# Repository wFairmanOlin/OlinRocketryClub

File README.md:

# OlinRocketryClub
Repo for a self-designed flight computer

## First Project - Phoenix I
1. 3-axis accelerometer
2. data storing functionality to SD card

## Second Project - Peregrine I
This board is intended to record flight data and transmit telemetry while maintaining a slim and lightweight profile.

### Main Components:
1. Barometer, Accelerometer, Gyroscope
2. Data storage to SD card
3. RF Transmitter
4. Battery

## How to Clone this Repo (Ubuntu)
1. Use the Ctrl+Alt+t command to open your terminal. 
2. Use the `cd` command to switch to the directory you want to save this repo in.
3. Copy and paste the code below into your terminal (hint: use Ctrl+Shift+v to paste into the terminal)
```
git clone https://github.com/wFairmanOlin/OlinRocketryClub.git
```

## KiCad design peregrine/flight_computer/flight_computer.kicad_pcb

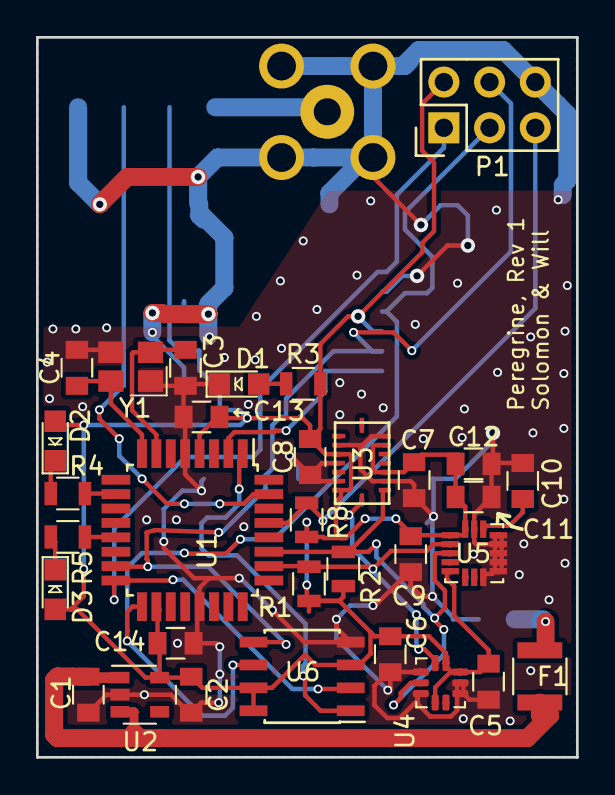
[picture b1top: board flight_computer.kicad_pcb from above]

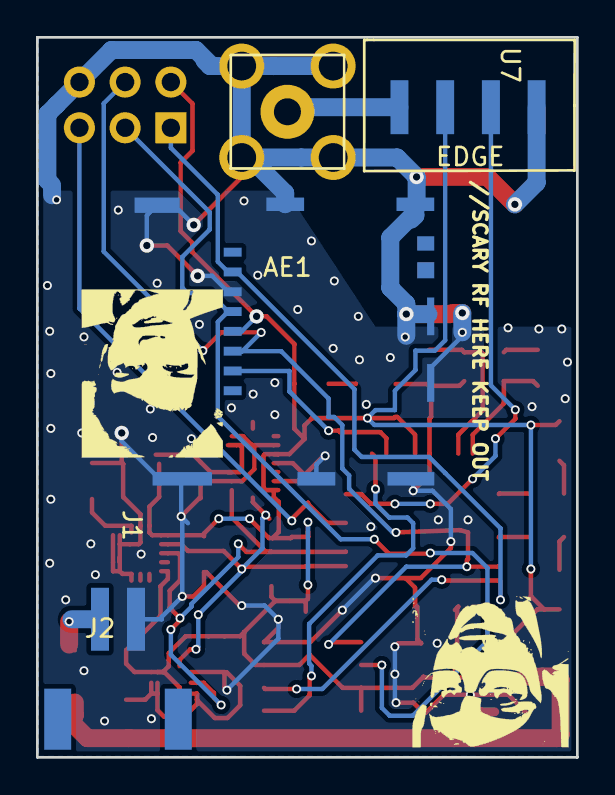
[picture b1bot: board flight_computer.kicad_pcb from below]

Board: 2 copper layers, 30.0 x 40.0 mm, 36 parts (4 on the bottom side), 22 nets.

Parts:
AE1: DS-SMA-EDGE-4; 5-1814400-1
C1, C2: C_1uF; C_0805_OEM
C3, C4: C_30pF; C_0805_OEM
C5, C6, C7, C8, C12, C14: C_0.1uF; C_0805_OEM
C9: 10nF; C_0805_OEM
C10: C_47uF; C_0805_OEM
C11: 2.2uF; C_0805_OEM
D1, D2, D3: LED_0805; LED_0805_OEM
F1: Fuse; Fuse_1210
J1: Micro_SD_Card_Det; SD-Card
J2: Conn_01x02_Male; JST_90DEG_2PIN
P1: CONN_02X03; Pin_Header_Straight_2x03
R1, R2: 4.7kR; R_0805_OEM
R3, R4, R5: R_200; R_0805_OEM
R8: R_10k; R_0805_OEM
U1: ATmega328PB-AU; TQFP-32_7x7mm_P0.8mm
U2: MIC5504-3.3YM5; SOT-23-5
U3: BMI088; BMI088-LGA16
U4: BMP388; ST_HLGA-10_2.5x2.5mm_P0.6mm_LayoutBorder3x2y
U5: ICG-20660; LGA-16_3x3mm_P0.5mm_LayoutBorder3x5y
U6: AT25SF041; SOIC-8_3.9x4.9mm_P1.27mm
U7: RFTRANS434MHZ
Y1: Crystal_SMD; Crystal_SMD_FA238
←C13: C_0.1uF; C_0805_OEM

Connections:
+3V3: C2.1, C5.1, C6.1, C7.2, C8.2, C9.1, C11.1, C12.1, C14.2, D2.2, D3.2, J1.4, P1.2, R1.1, R2.1, R3.2, R8.1, U1.4, U1.18, U2.5, U3.3, U3.7, U3.11, U3.14, U4.1, U4.6, U4.10, U5.1, U5.5, U5.16, U6.3, U6.7, U6.8, U7.3, ←C13.1
+BATT: C1.1, F1.1, U2.1, U2.3
/CS_FLASH: U1.1, U6.1
/CS_SD: J1.2, U1.2
/LED_B: R4.2, U1.10
/LED_R: R5.2, U1.13
/MISO: J1.7, P1.1, U1.16, U6.2
/MOSI: J1.3, P1.4, U1.15, U6.5
/RST: P1.5, R8.2, U1.29
/SCK: J1.5, P1.3, U1.17, U6.6
/SCL: R1.2, U1.26, U3.8, U4.2, U5.2
/SDA: R2.2, U1.27, U3.9, U4.4, U5.3
/TXD: U1.31, U7.2
/XTAL1: C3.1, U1.7, Y1.1
/XTAL2: C4.1, U1.8, Y1.3
GND: AE1.2, C1.2, C2.2, C3.2, C4.2, C5.2, C6.2, C7.1, C8.1, C9.2, C10.2, C11.2, C12.2, C14.1, D1.1, J1.6, J1.11, J2.2, P1.6, U1.5, U1.21, U2.2, U3.2, U3.4, U3.6, U3.10, U3.15, U4.3, U4.5, U4.8, U4.9, U5.8, U5.9, U5.10, U5.11, U5.12, U5.13, U5.15, U6.4, U7.1, Y1.2, Y1.4, ←C13.2
unnamed: AE1.1, U7.4
unnamed: C10.1, U5.14
unnamed: D1.2, R3.1
unnamed: D2.1, R4.1
unnamed: D3.1, R5.1
unnamed: F1.2, J2.1

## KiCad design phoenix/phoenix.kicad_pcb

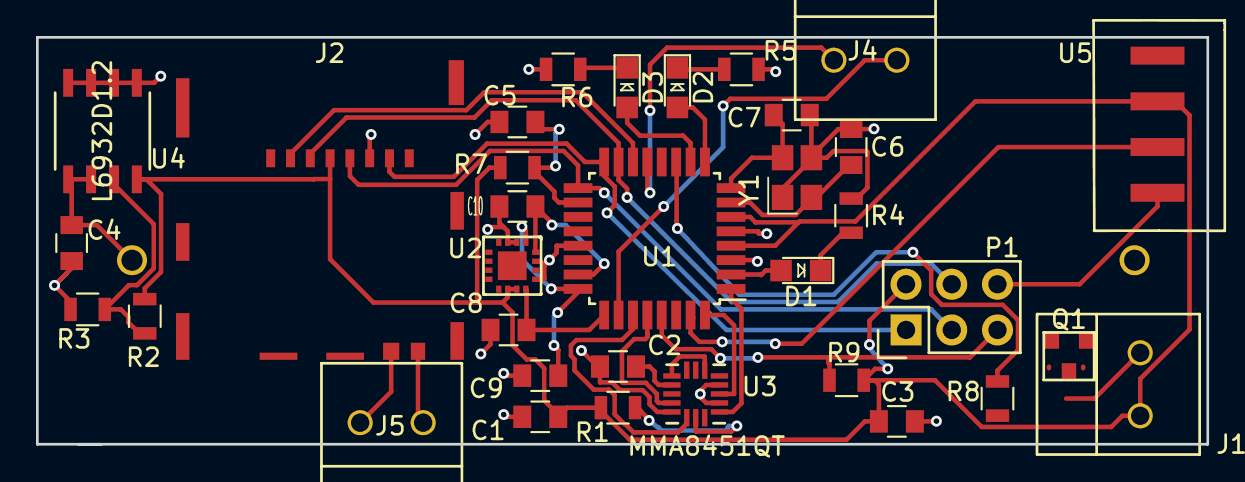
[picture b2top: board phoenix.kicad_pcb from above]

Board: 2 copper layers, 65.0 x 22.6 mm, 35 parts (1 on the bottom side), 35 nets.

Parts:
BT1: 3.7V Lipo; battery_holder
C1, C2: C_0.1uF; C_0805_OEM
C3, C4: C_10uF; C_0805_OEM
C5: C_100pF; C_0805_OEM
C6, C7: C_30pF; C_0805_OEM
C8, C9, C10: C_1000pF; C_0805_OEM
D1, D2, D3: LED_0805; LED_0805_OEM
J1, J4, J5: Ultrafit_2
J2: Micro_SD_Card_Det; SD-Card
P1: CONN_02X03; Pin_Header_Straight_2x03
Q1: IRLML6344; IRLML6344TRPBFCT-ND
R1, R8, R9: R_10k; R_0805_OEM
R2: 9K; R_0805_OEM
R3: 5K; R_0805_OEM
R4, R5, R6: R_200; R_0805_OEM
R7: R_100; R_0805_OEM
U1: ATMEGA328P-AU; TQFP-32_7x7mm_Pitch0.8mm
U2: ADX377; ADXL377
U3: MMA8451QT
U4: L6932D1.2; L6932D1.2TR
U5: RFTRANS434MHZ
Y1: Crystal_SMD; Crystal_SMD_FA238

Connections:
+3V3: C1.1, C3.1, J1.1, J2.4, P1.2, R1.2, R2.1, R7.1, R9.1, U1.4, U1.6, U2.14, U2.15, U4.4, U5.3
/BYP: C2.1, U3.2
/INT1: U1.32, U3.11
/INT2: U1.1, U3.9
/MISO: J2.7, P1.1, U1.16
/MOSI: J2.3, P1.4, U1.15
/PB6: C6.1, U1.7, Y1.1
/PB7: C7.1, U1.8, Y1.3
/PLED1: D1.2, U1.2
/PLED2: D2.2, U1.9
/PLED3: D3.2, U1.10
/RESET: P1.5, R9.2, U1.29
/SCK: J2.5, P1.3, U1.17
/SCL: U1.28, U3.4
/SDA: U1.27, U3.6
/SEPERATE: Q1.1, R8.1, U1.11
/Spi_config: J2.2, U1.14
/TX: U1.31, U5.2
/VIN: BT1.1, C4.1, U4.1, U4.2
/XOUT: C9.1, U1.24, U2.5
/YOUT: C10.1, U1.23, U2.4
/ZOUT: C8.1, U1.25, U2.16
GND: BT1.2, C1.2, C2.2, C3.2, C4.2, C5.2, C6.2, C7.2, C8.2, C9.2, C10.2, J2.6, P1.6, Q1.2, R3.2, R4.2, R5.2, R6.2, R8.2, U1.3, U1.5, U1.21, U2.1, U2.3, U2.6, U2.7, U3.5, U3.10, U3.12, U4.5, U4.6, U4.7, U4.8, U5.1, Y1.2, Y1.4
unnamed: C5.1, R7.2, U1.18
unnamed: D1.1, R4.1
unnamed: D2.1, R5.1
unnamed: D3.1, R6.1
unnamed: J1.2, Q1.3
unnamed: J2.9, J5.2
unnamed: J2.10, J5.1
unnamed: R1.1, U3.7
unnamed: R2.2, R3.1, U4.3
unnamed: J4.1, U1.13
unnamed: J4.2, U1.26
unnamed: U3.1, U3.14

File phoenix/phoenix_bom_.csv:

Component,Description,Part,References,Value,Footprint,Quantity Per PCB,Datasheet,Package,MPN,MFN,PurchasingLink,PurchasingLinks
1,single battery cell,Battery_Cell,BT1,3.7V Lipo,battery_holder,1,,,,,,
2,,C_0.1uF,C1 C2,C_0.1uF,C_0805_OEM,2,http://datasheets.avx.com/X7RDielectric.pdf,Value,478-3352-1-ND,Digi-Key,https://www.digikey.com/products/en?keywords=478-3352-1-ND,
3,,C_100pF,C5,C_100pF,C_0805_OEM,1,https://content.kemet.com/datasheets/KEM_C1003_C0G_SMD.pdf,Value,399-1122-1-ND,Digi-Key,https://www.digikey.com/product-detail/en/kemet/C0805C101J5G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,
4,,C_10uF,C3 C4,C_10uF,C_0805_OEM,2,http://datasheets.avx.com/cx5r.pdf,Value,478-5167-1-ND,Digi-Key,https://www.digikey.com/product-detail/en/avx-corporation/08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,
5,,C_30pF,C6 C7,C_30pF,C_0805_OEM,2,https://media.digikey.com/pdf/Data%20Sheets/Samsung%20PDFs/C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,Value,1276-1130-1-ND,Digi-Key,https://www.digikey.com/product-detail/en/samsung-electro-me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,
6,,LED_0805,D1 D2 D3,LED_0805,LED_0805_OEM,3,http://www.osram-os.com/Graphics/XPic9/00078860_0.pdf,Value,475-1410-1-ND,Digi-Key,https://www.digikey.com/products/en?keywords=475-1410-1-ND,
7,Micro SD Card Socket with card detection pins,Micro_SD_Card_Det,J2,Micro_SD_Card_Det,SD-Card,1,https://www.hirose.com/product/en/download_file/key_name/DM3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,,,,,
8,,Ultrafit_2,J1,Ultrafit_2,Ultrafit_2_RA,1,,Value,WM11570-ND,Digi-Key,https://www.digikey.com/product-detail/en/molex-llc/17228611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,
9,,CONN_02X03,P1,CONN_02X03,Pin_Header_Straight_2x03,1,http://portal.fciconnect.com/Comergent//fci/drawing/67996.pdf,Value,609-3234-ND,Digi-Key,https://www.digikey.com/product-detail/en/amphenol-fci/67997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,
10,"200V Vds, N-Channel MOSFET, 2.6V Logic Level, TO-92",IRLML6344,Q1,IRLML6344,IRLML6344TRPBFCT-ND,1,https://www.infineon.com/dgdl/irlml6344pbf.pdf?fileId=5546d4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,,,,,https://www.digikey.com/product-detail/en/infineon-technolog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
11,,5K,R3,5K,R_0805_OEM,1,,,,,,
12,,5K,R2,9K,R_0805_OEM,1,,,,,,
13,,R_100,R7,R_100,R_0805_OEM,1,https://www.seielect.com/Catalog/SEI-rncp.pdf,Value,RNCP0805FTD100RCT-ND,Digi-Key,https://www.digikey.com/products/en?keywords=RNCP0805FTD100RCT-ND,
14,,R_10k,R1 R8 R9,R_10k,R_0805_OEM,3,http://www.bourns.com/data/global/pdfs/CRS.pdf,Value,CRS0805-FX-1002ELFCT-ND,Digi-Key,https://www.digikey.com/products/en?keywords=CRS0805-FX-1002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,
15,,R_200,R4 R5 R6,R_200,R_0805_OEM,3,https://www.seielect.com/Catalog/SEI-RMCF_RMCP.pdf,Value,RMCF0805JT200RCT-ND,Digi-Key,https://www.digikey.com/products/en?keywords=RMCF0805JT200RCT-ND,
16,"TQFP32, 16k Flash, 1kB SRAM, 512B EEPROM",ATMEGA328P-AU,U1,ATMEGA328P-AU,TQFP-32_7x7mm_Pitch0.8mm,1,http://www.atmel.com/images/atmel-8271-8-bit-avr-microcontro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,,,,,
17,,L6932D1.2,U4,L6932D1.2,L6932D1.2TR,1,,,,,,
18,,MMA8451QT,U3,MMA8451QT,MMA8451QT,1,,,,,,https://www.digikey.com/products/en?mpart=MMA8451QT&v=568
19,,Crystal_SMD,Y1,Crystal_SMD,Crystal_SMD_FA238,1,https://support.epson.biz/td/api/doc_check.php?dl=brief_FA-2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,Value,SER3686CT-ND,Digi-Key,https://www.digikey.com/products/en?keywords=SER3686CT-ND,





Component Groups:,19
Component Count:,28
Fitted Components:,28
Number of PCBs:,1
Total components:,28
Schematic Version:,
Schematic Date:,
BoM Date:,Thu 12 Apr 2018 10:37:11 PM EDT
Schematic Source:,/home/william/Desktop/OlinRocketryClub/phoenix/phoenix.sch
KiCad Version:,Eeschema 4.0.7-e2-6376~58~ubuntu16.04.1

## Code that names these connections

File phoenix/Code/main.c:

#include <avr/io.h>
#include <util/delay.h>
#include <avr/interrupt.h>

#define F_CPU           4000000UL
#define PORT_LED        PORTD
#define REG_LED         DDRD
#define LED1            PD4
#define LED2            PD5
#define LED3            PD6

#define PORT_A          PORTC
#define REG_A           DDRC
#define YOUT            PC0
#define XOUT            PC1
#define ZOUT            PC2

#define FLAG_EMATCH     0

uint8_t gFlag = 0x00;

uint8_t gY = 0x00;
uint8_t gX = 0x00;
uint8_t gZ = 0x00;

unsigned long gCounter = 0x00;

/* TODO FOR WEDNESDAY */
//Get timer working
//Write to sd-card
//Get transistor working
//Calibrate accelerometer data
//Create function for appogee using accel data

ISR(TIMER0_COMPA_vect){
    //TODO fix
    //Currently ticks at 4hz
    gCounter++;
    if (gCounter > 60){
        gFlag |= _BV(FLAG_EMATCH);
    }
    if(gCounter > 80){
        gFlag |= _BV(3);
    }

}

void initTimer(void) {
    //TODO
    //FOR 16M1, configure for 328P
    TCCR0A = _BV(WGM01);    // Set up 8-bit timer in CTC mode
    TCCR0B = 0x05;          // clkio/1024 prescaler
    TIMSK0 |= _BV(OCIE0A);
    OCR0A = 0xFF;
}


void initADC(void) {
    //Get the Analog to Digital Converter started (ADC)
    ADCSRA |= _BV(ADEN) | _BV(ADPS2) | _BV(ADPS0);

    //Enable interal reference voltage
    // ADCSRB |= _BV(AREFEN);

    //Set internal reference voltage as AVcc
    ADMUX |= _BV(REFS0);

    //Reads by default from ADC0 (pin 11)
    //This line is redundant. The timer
    ADMUX |= _BV(0x00);
}

void readAC(void){
    ADMUX = _BV(REFS0);
    ADMUX |= 0;
    ADCSRA |= _BV(ADSC);
    loop_until_bit_is_clear(ADCSRA, ADSC);
    gY = (uint8_t) (ADC >> 2);


    ADMUX = _BV(REFS0);
    ADMUX |= 1;
    ADCSRA |= _BV(ADSC);
    loop_until_bit_is_clear(ADCSRA, ADSC);
    gX = (uint8_t) (ADC >> 2);


    ADMUX = _BV(REFS0);
    ADMUX |= 2;
    ADCSRA |= _BV(ADSC);
    loop_until_bit_is_clear(ADCSRA, ADSC);
    gZ = (uint8_t) (ADC >> 2);

    if(gX > 128){
        PORT_LED |= _BV(LED1);
    } else {
        PORT_LED &= ~_BV(LED1);
    }

    if(gY > 128){
        PORT_LED |= _BV(LED2);
    } else {
        PORT_LED &= ~_BV(LED2);
    }

    if(gZ > 128){
        PORT_LED |= _BV(LED3);
    } else {
        PORT_LED &= ~_BV(LED3);
    }
}

void triggerEMatch(void){

}

int main (void) {

    sei();
    initADC();
    initTimer();


    REG_LED |= _BV(LED1) | _BV(LED2) | _BV(LED3);
    DDRD |= _BV(PD7);
    PORT_LED |= _BV(LED3);
    // uint8_t count = 0;
    while(1) {
        // count++;
        // readAC();


        if(bit_is_set(gFlag,FLAG_EMATCH)){
            PORT_LED |= _BV(LED1);
            PORTD |= _BV(PD7);
        }

        if(bit_is_set(gFlag,3)){
            PORT_LED |= _BV(LED2);
        }



    }
}

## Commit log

2018-02-16 added goals of first project
2018-02-16 modified README
2018-02-19 started a kicad project and added datasheets for some components
2018-02-25 added more datasheets
2018-02-26 added a list of purchasing links for a bread board flight computer
2018-02-28 added final parts for breadboard version
2018-03-12 Add PCB cad file
    -Start footprints.pretty folder
    -Add battery_holder footprint
    -Add programming header footprint
2018-03-13 Add link to sparkplug with mosfet
2018-03-16 added components
2018-03-16 included goal
2018-03-16 Snacks
2018-03-27 added more components to the library and also included all of formula's components to the library
2018-03-28 Updated schematic
2018-03-28 added more parts to purchasing links
2018-04-02 added RF beacons for prototyping
2018-04-03 added components to board
2018-04-04 added more parts
2018-04-06 created documentation for flight computer
    there were too many notes at the top of the arduino code...
2018-04-06 Added basic start to arduino code
    Includes IMU to SD card datalogging and note much else
2018-04-12 Added external oscillator
2018-04-12 Edited schematic and added footpring
2018-04-12 new footprints
2018-04-12 Started layout
2018-04-12 fixed power transistor. Added to layout
2018-04-13 more partsgit add *
2018-04-13 added new accelerometer
2018-04-13 added more labels
2018-04-15 deleted something
2018-04-15 more components
2018-04-15 fixed footprint
2018-04-16 Draft layout
    Added:
    -changes to layout
    -drafted tracing
    -modified some footprints
    -added 3d-file for micro-sd-card slot
2018-04-16 Update layout and tracing
2018-04-16 Fix references
    stuuf
2018-04-22 Set theme jekyll-theme-slate
2018-04-22 Create CNAME
2018-04-24 Start C code for board
2018-04-25 arduino sketch, slightly updated.
2018-04-28 draft make file
2018-04-28 added avr library
2018-04-29 Update non-working code for computer
2018-05-01 First good code for board
2018-05-01 Add C code for computer
2018-05-02 Add schematic pictures
2018-05-02 Cleanup
2018-09-15 update to kicad 5
2018-09-16 added test.ino files
2018-09-16 added readme from 9/16 testing
2018-09-19 Component selection
2018-09-26 Updated schematic & footprints
2018-10-03 Finished schematic + footprints ==> starting on layout
2018-10-17 Final rev?
2018-10-17 Jesus help me

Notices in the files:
parts and their libraries:
Copyright 2016 Accelerated Designs. All rights reserved.
